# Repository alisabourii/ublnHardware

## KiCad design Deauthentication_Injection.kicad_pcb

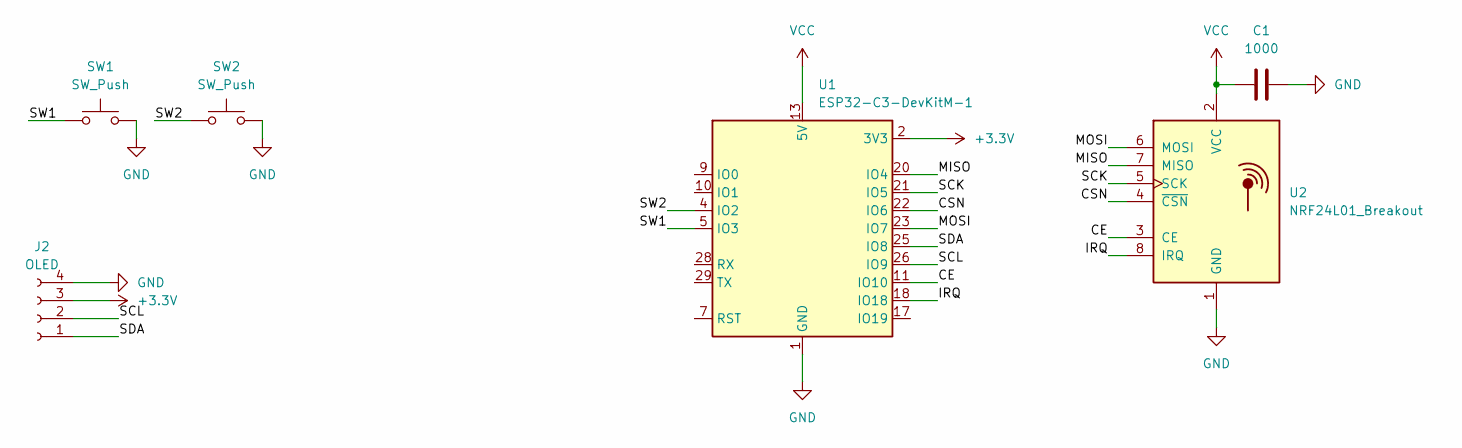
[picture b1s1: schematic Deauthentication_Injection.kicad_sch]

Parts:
C1: 1000; CP_Radial_D14.0mm_P5.00mm
J2: OLED; Molex_SL_171971-0004_1x04_P2.54mm_Vertical
SW1, SW2: SW_Push; SW_PUSH_6mm_H8.5mm
U1: ESP32-C3-DevKitM-1
U2: NRF24L01_Breakout; nRF24L01_Breakout

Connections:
+3.3V: J2.3, U1.2 (3V3), U1.3 (3V3)
/CE: U1.11 (IO10), U2.3 (CE)
/CSN: U1.22 (IO6), U2.4 (~CSN)
/IRQ: U1.18 (IO18), U2.8 (IRQ)
/MISO: U1.20 (IO4), U2.7 (MISO)
/MOSI: U1.23 (IO7), U2.6 (MOSI)
/SCK: U1.21 (IO5), U2.5 (SCK)
/SCL: J2.2, U1.26 (IO9)
/SDA: J2.1, U1.25 (IO8)
/SW1: SW1.1, U1.5 (IO3)
/SW2: SW2.1, U1.4 (IO2)
GND: C1.1, J2.4, SW1.2, SW2.2, U1.1 (GND), U1.6 (GND), U1.8 (GND), U1.12 (GND), U1.15 (GND), U1.16 (GND), U1.19 (GND), U1.24 (GND), U1.27 (GND), U1.30 (GND), U2.1 (GND)
VCC: C1.2, U1.13 (5V), U1.14 (5V), U2.2 (VCC)

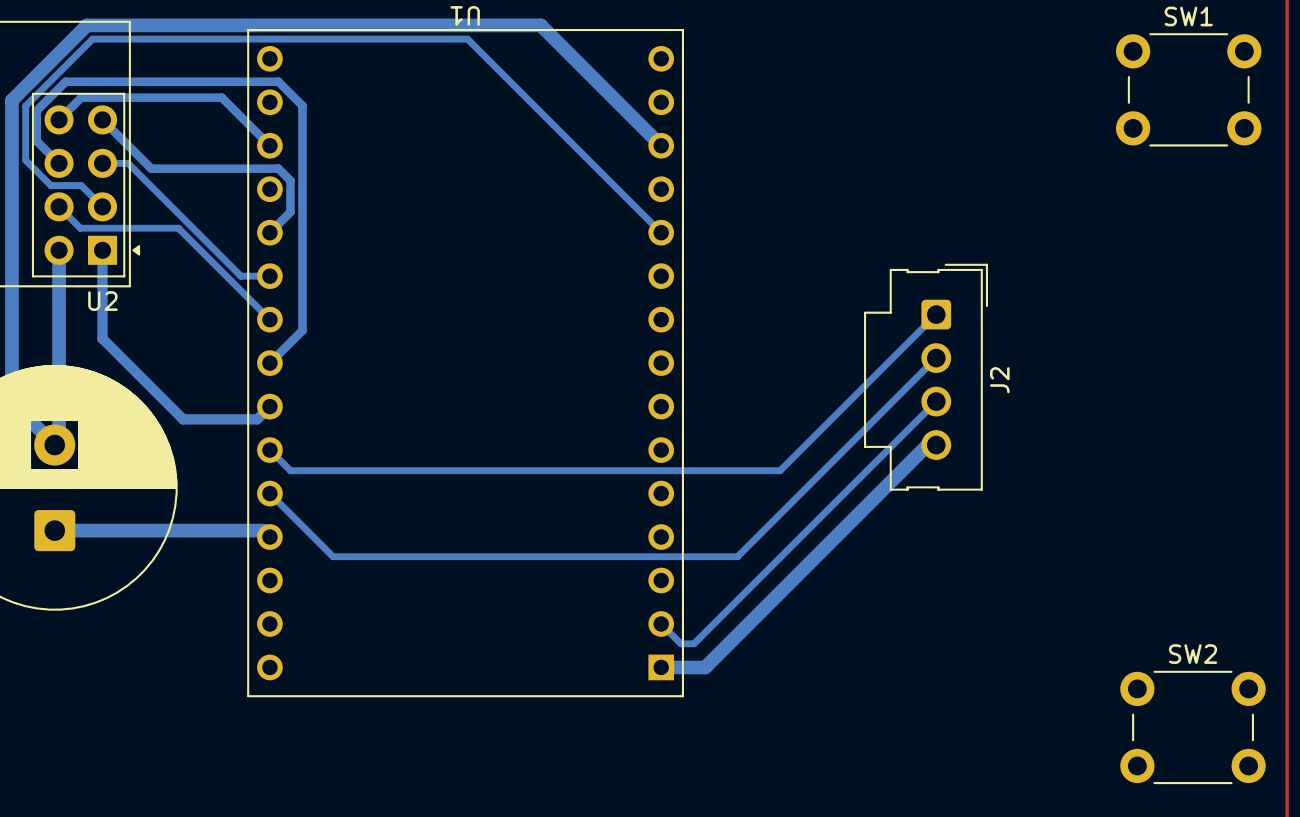
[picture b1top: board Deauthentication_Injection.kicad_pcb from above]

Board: 2 copper layers, 6 parts (0 on the bottom side), 13 nets.
